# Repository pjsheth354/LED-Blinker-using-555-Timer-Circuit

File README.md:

# LED-Blinker-using-555-Timer-Circuit
A simple and educational electronics project demonstrating a reliable LED blinker circuit. This project uses the versatile 555 timer IC in an astable configuration to generate a continuous square wave output. The blinking frequency can be easily adjusted with the RC network. Perfect for beginners learning fundamental electronics.

This project is designed in KiCAD 9.0 PCB design software.

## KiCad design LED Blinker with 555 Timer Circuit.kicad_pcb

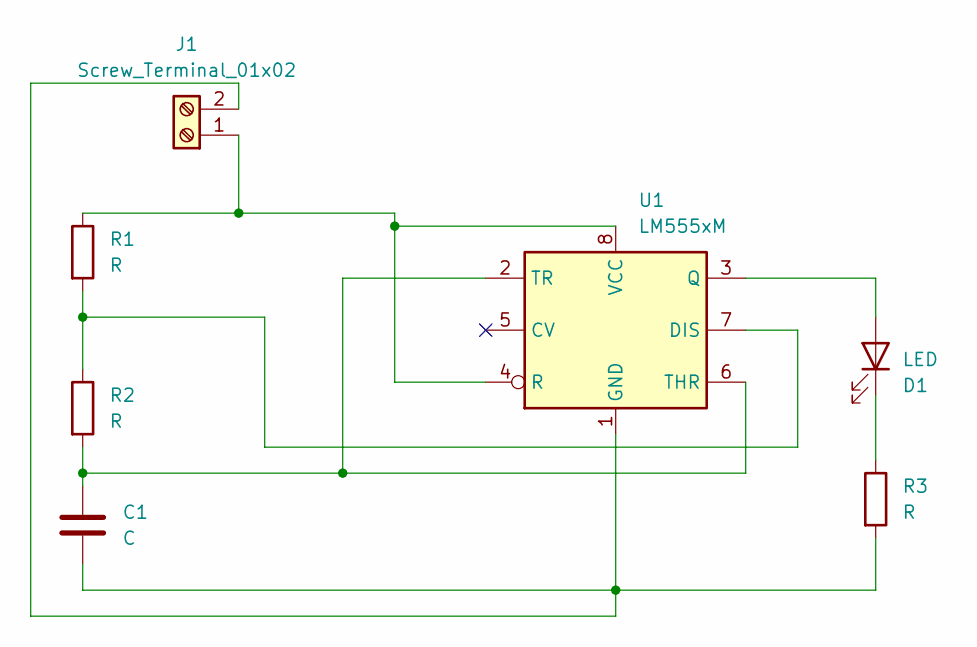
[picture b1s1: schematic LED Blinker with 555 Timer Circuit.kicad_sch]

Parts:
C1: C; CP_Radial_D4.0mm_P1.50mm
D1: LED; LED_D3.0mm
J1: Screw_Terminal_01x02; PhoenixContact_MCV_1,5_2-G-5.08_1x02_P5.08mm_Vertical
R1, R2, R3: R; R_Axial_DIN0204_L3.6mm_D1.6mm_P5.08mm_Horizontal
U1: LM555xM; SOIC-8_3.9x4.9mm_P1.27mm

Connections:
unnamed: D1.2 (A), U1.3 (Q)
unnamed: D1.1 (K), R3.1
unnamed: J1.1, R1.1, U1.4 (R), U1.8 (VCC)
unnamed: C1.2, J1.2, R3.2, U1.1 (GND)
unnamed: R1.2, R2.1, U1.7 (DIS)
unnamed: C1.1, R2.2, U1.2 (TR), U1.6 (THR)

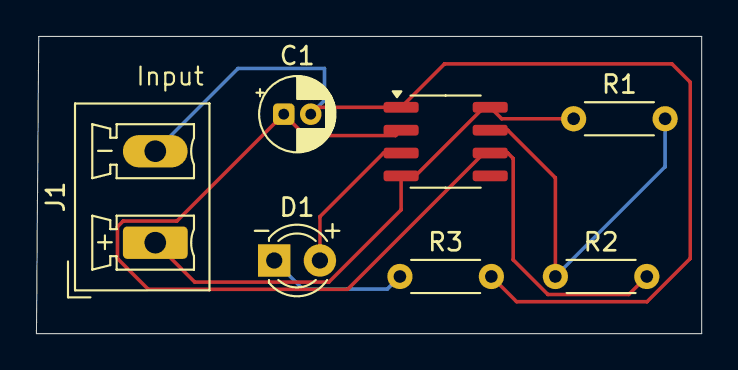
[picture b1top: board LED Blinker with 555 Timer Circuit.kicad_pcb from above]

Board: 2 copper layers, 37.0 x 16.5 mm, 7 parts (0 on the bottom side), 6 nets.
